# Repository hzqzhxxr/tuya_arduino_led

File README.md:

# tuya_arduino_led
This project is developed using Tuya SDK, which enables you to quickly develop branded apps connecting and controlling smart scenarios of many devices.

For more information, please check Tuya Developer Website.

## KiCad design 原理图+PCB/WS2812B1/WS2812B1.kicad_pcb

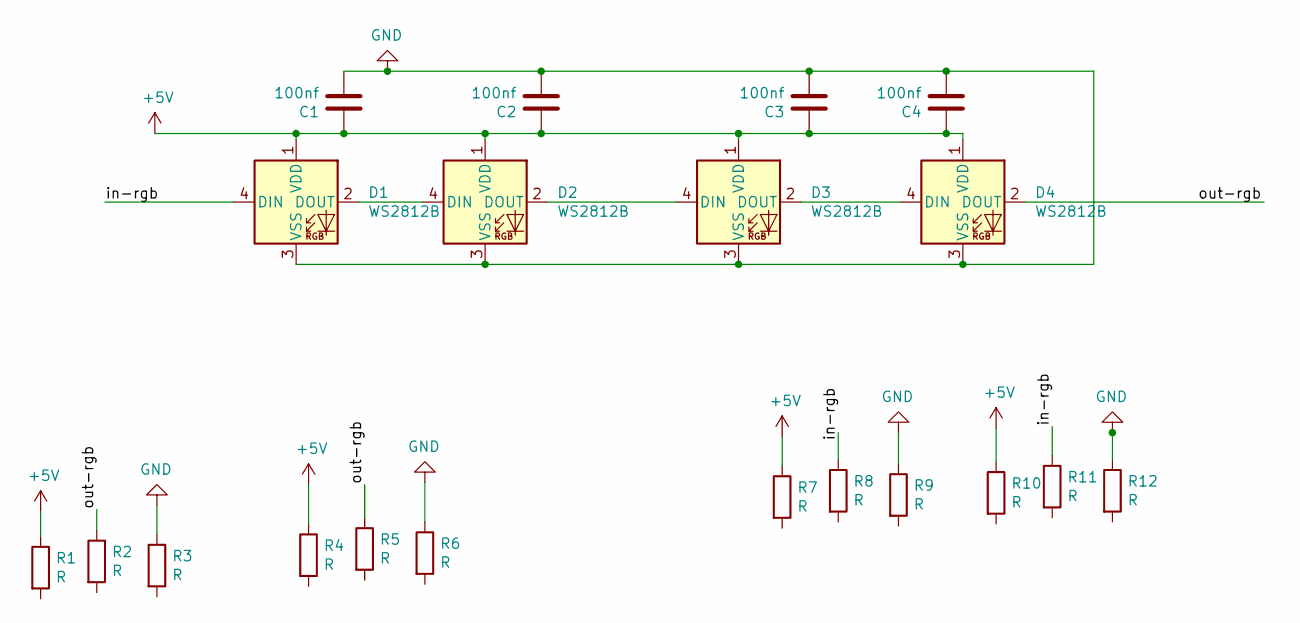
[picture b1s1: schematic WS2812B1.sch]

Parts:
C1, C2, C3, C4: 100nf; C_0603_1608Metric_Pad1.08x0.95mm_HandSolder
D1, D2, D3, D4: WS2812B; LED_WS2812B_PLCC4_5.0x5.0mm_P3.2mm
R1, R2, R3, R4, R5, R6, R7, R8, R9, R10, R11, R12: R; 焊接连接电阻

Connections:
+5V: C1.1, C2.1, C3.1, C4.1, D1.1 (VDD), D2.1 (VDD), D3.1 (VDD), D4.1 (VDD), R1.1, R4.1, R7.1, R10.1
/in-rgb: D1.4 (DIN), R8.1, R11.1
/out-rgb: D4.2 (DOUT), R2.1, R5.1
GND: C1.2, C2.2, C3.2, C4.2, D1.3 (VSS), D2.3 (VSS), D3.3 (VSS), D4.3 (VSS), R3.1, R6.1, R9.1, R12.1
unnamed: D1.2 (DOUT), D2.4 (DIN)
unnamed: D2.2 (DOUT), D3.4 (DIN)
unnamed: D3.2 (DOUT), D4.4 (DIN)

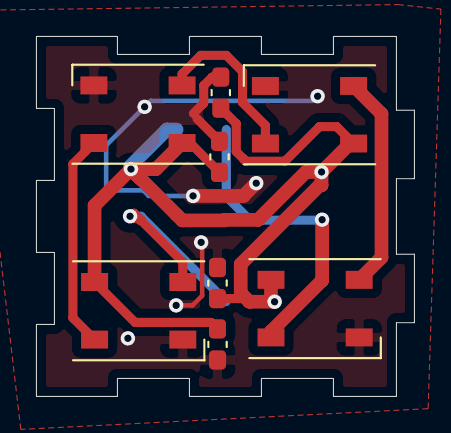
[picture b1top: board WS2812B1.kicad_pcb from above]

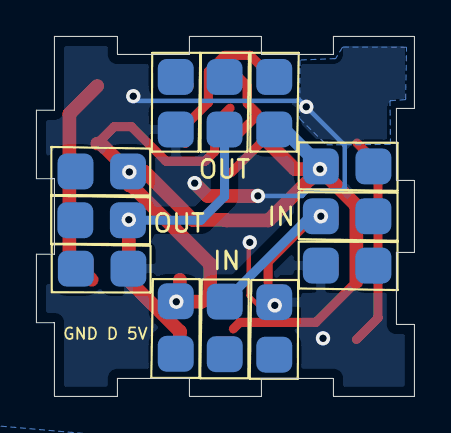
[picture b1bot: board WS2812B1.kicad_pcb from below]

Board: 2 copper layers, 21.0 x 20.0 mm, 20 parts (12 on the bottom side), 7 nets.

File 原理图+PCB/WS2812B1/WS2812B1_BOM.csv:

"Comment","Description","Designator","Footprint","LibRef","Pins","Quantity","PartNumber","url",
"100nf","desc","C1,C2,C3,C4,","C_0603_1608Metric_Pad1.08x0.95mm_HandSolder","libref","2","4","","",
"WS2812B","desc","D1,D2,D3,D4,","LED_WS2812B_PLCC4_5.0x5.0mm_P3.2mm","libref","4","4","","",
"Through Hole Items ",
"R","desc","R1,R2,R3,R4,R5,R6,R7,R8,R9,R10,R11,R12,","焊接连接电阻","libref","2","12","","",

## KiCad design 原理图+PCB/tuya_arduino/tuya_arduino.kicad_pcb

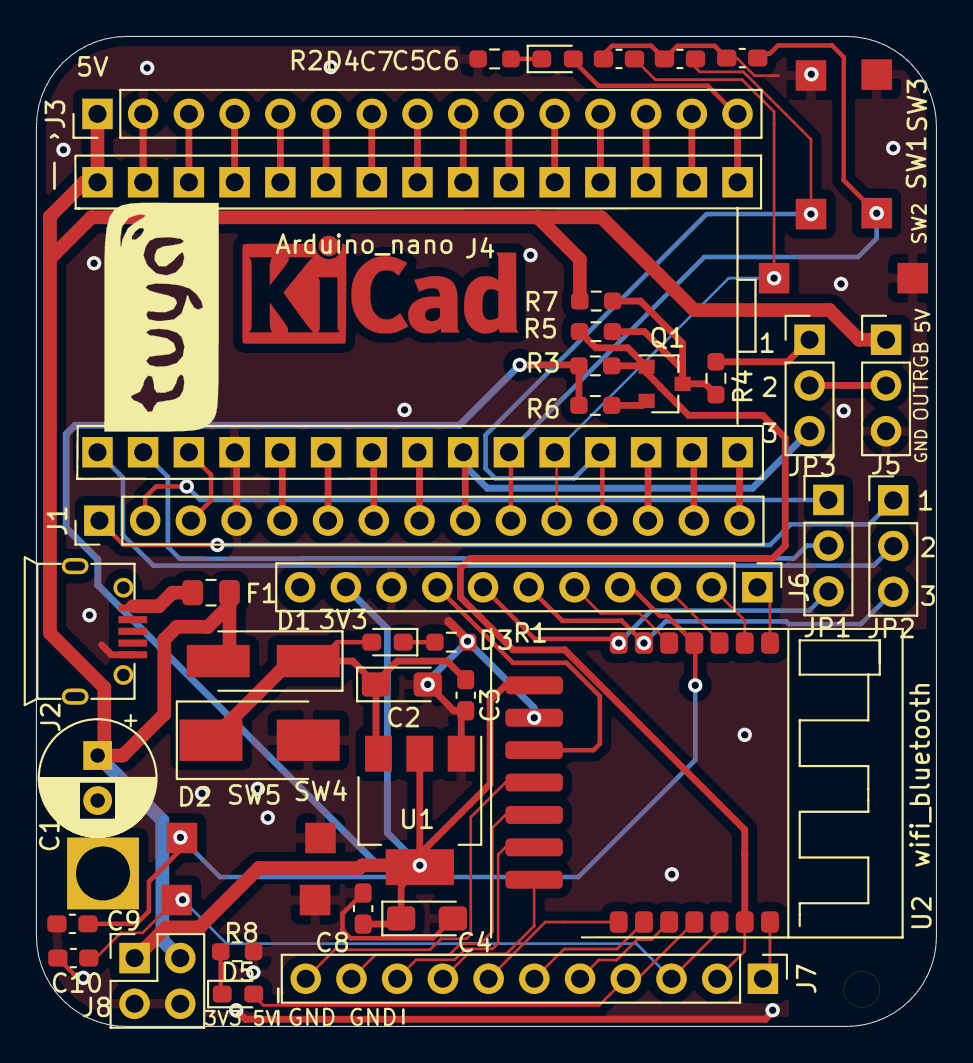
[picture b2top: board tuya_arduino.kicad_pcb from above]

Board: 2 copper layers, 50.0 x 55.0 mm, 43 parts (0 on the bottom side), 60 nets.

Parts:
C1: 220uf; CP_Radial_D6.3mm_P2.50mm
C2, C4: 22uf; CP_EIA-3216-18_Kemet-A_Pad1.58x1.35mm_HandSolder
C3, C5, C6, C7, C8, C9, C10: 0.1uf; C_0603_1608Metric_Pad1.08x0.95mm_HandSolder
D1: ss210; D_SMA_Handsoldering
D2: D_Zener; D_SMB_Handsoldering
D3, D4, D5: LED; LED_0603_1608Metric_Pad1.05x0.95mm_HandSolder
F1: Fuse; Fuse_0805_2012Metric_Pad1.15x1.40mm_HandSolder
J1, J3: Conn_01x15_Male; PinHeader_1x15_P2.54mm_Vertical
J2: USB_A; MicroUSB_5S_B_A01SB141B1-067
J4: arduino_nano_base; Arduino_nano_base
J5: Conn_01x03_Female; PinHeader_1x03_P2.54mm_Vertical
J6, J7: Conn_01x11_Male; PinHeader_1x11_P2.54mm_Vertical
J8: Conn_02x02_Top_Bottom_MountingPin; PinHeader_2x02_P2.54mm_Vertical
JP1, JP2, JP3: Jumper_NC_Dual; PinHeader_1x03_P2.54mm_Vertical
Q1: S8050; SOT-23
R1, R2: 330; R_0603_1608Metric_Pad0.98x0.95mm_HandSolder
R3, R6, R7: 2k; R_0603_1608Metric_Pad0.98x0.95mm_HandSolder
R4: 1R; R_0603_1608Metric_Pad0.98x0.95mm_HandSolder
R5: NC/0R; R_0603_1608Metric_Pad0.98x0.95mm_HandSolder
R8: 220; R_0603_1608Metric_Pad0.98x0.95mm_HandSolder
SW1, SW2, SW3, SW4, SW5: SW_Push; button_smd
U1: AMS1117-3.3; SOT-223-3_TabPin2
U2: mcu_tuya_cbu; tuya_cbu

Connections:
+3V3: C4.1, C8.1, J6.10, J8.1, R3.1, R6.1, U1.2, U2.14
+5V: C1.1, D1.2, F1.1, J3.1, J4.30, J5.1, J8.2, R7.1
/3V3: J3.14, J4.17
/5V: J3.4, J4.27
/A0: J3.12, J4.19
/A1: J3.11, J4.20
/A2: J3.10, J4.21
/A3: J3.9, J4.22
/A4: J3.8, J4.23
/A5: J3.7, J4.24
/A6: J3.6, J4.25
/A7: J3.5, J4.26
/ADC: J7.5, U2.5
/AREF: J3.13, J4.18
/D2: J1.5, J4.5
/D3: J1.6, J4.6
/D4: J1.7, J4.7
/D5: J1.8, J4.8
/D6: J1.9, J4.9, JP3.3
/D7: C6.1, J1.10, J4.10, SW3.1
/D8: C7.1, J1.11, J4.11, SW2.1
/D9: C5.1, J1.12, J4.12, SW1.1
/D10: J1.13, J4.13
/D11: J1.14, J4.14
/D12: J1.15, J4.15
/D13: D4.2, J3.15, J4.16
/KEY_TU: C10.1, J7.3, SW4.1, U2.3
/OUT_RGB: J5.2, JP3.2
/OUT_RGB_TU_3V3: J7.2, Q1.1, R3.2, R5.1, U2.2
/OUT_RGB_TU_5V: Q1.3, R4.1, R5.2, R7.2
/P6: J7.10, U2.10
/P7: J7.9, U2.9
/P8: J7.8, U2.8
/P9: J6.3, U2.19
/P14: J7.1, U2.1
/P15: J6.1, U2.21
/P17: J6.2, U2.20
/P22: D5.2, J7.4, U2.4
/P24: J6.8, U2.12
/P26: J7.11, U2.11
/P28: J6.5, U2.17
/RESET: J3.3, J4.28
/RST: J1.3, J4.3
/RST_TU,CEN: C9.1, J6.4, SW5.1, U2.18
/RX: J4.2, JP1.2
/RX2: J7.6, U2.6
/RX_C: J6.6, JP2.3, U2.16
/RX_D: J1.2, JP1.1
/TX: J4.1, JP2.2
/TX2: J7.7, U2.7
/TX_C: J6.7, JP1.3, U2.15
/TX_D: J1.1, JP2.1
GND: C2.2, C3.2, C4.2, C5.2, C6.2, C7.2, C8.2, C9.2, C10.2, D2.2, J1.4, J2.5, J3.2, J4.4, J4.29, J5.3, J6.9, J8.3, J8.4, R1.2, R2.2, R8.2, SW1.2, SW2.2, SW3.2, SW4.2, SW5.2, U1.1, U2.13
unnamed: C2.1, C3.1, D1.1, D2.1, D3.2, U1.3
unnamed: D3.1, R1.1
unnamed: D4.1, R2.1
unnamed: D5.1, R8.1
unnamed: F1.2, J2.1
unnamed: JP3.1, R4.2
unnamed: Q1.2, R6.2

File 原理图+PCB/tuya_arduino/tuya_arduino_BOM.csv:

"Comment","Description","Designator","Footprint","LibRef","Pins","Quantity","PartNumber","url",
"22uf","desc","C2,C4,","CP_EIA-3216-18_Kemet-A_Pad1.58x1.35mm_HandSolder","libref","2","2","","",
"0.1uf","desc","C3,C5,C6,C7,C8,C9,C10,","C_0603_1608Metric_Pad1.08x0.95mm_HandSolder","libref","2","7","","",
"ss210","desc","D1,","D_SMA_Handsoldering","libref","2","1","","",
"D_Zener","desc","D2,","D_SMB_Handsoldering","libref","2","1","","",
"LED","desc","D3,D4,D5,","LED_0603_1608Metric_Pad1.05x0.95mm_HandSolder","libref","2","3","","",
"Fuse","desc","F1,","Fuse_0805_2012Metric_Pad1.15x1.40mm_HandSolder","libref","2","1","","",
"S8050","desc","Q1,","SOT-23","libref","3","1","","",
"330","desc","R1,R2,","R_0603_1608Metric_Pad0.98x0.95mm_HandSolder","libref","2","2","","",
"2k","desc","R3,R6,R7,","R_0603_1608Metric_Pad0.98x0.95mm_HandSolder","libref","2","3","","",
"1R","desc","R4,","R_0603_1608Metric_Pad0.98x0.95mm_HandSolder","libref","2","1","","",
"NC/0R","desc","R5,","R_0603_1608Metric_Pad0.98x0.95mm_HandSolder","libref","2","1","","",
"220","desc","R8,","R_0603_1608Metric_Pad0.98x0.95mm_HandSolder","libref","2","1","","",
"AMS1117-3.3","desc","U1,","SOT-223-3_TabPin2","libref","4","1","","",
"mcu_tuya_cbu","desc","U2,","tuya_cbu","libref","21","1","","",
"SW_Push","desc","SW1,SW2,SW3,SW4,SW5,","button_smd","libref","2","5","","",
"LOGO","desc","G***,","tuya-logo","libref","0","1","","",
"KiCad-Logo_6mm_Copper","desc","REF**,","KiCad-Logo_6mm_Copper","libref","0","1","","",
"Through Hole Items ",
"220uf","desc","C1,","CP_Radial_D6.3mm_P2.50mm","libref","2","1","","",
"Conn_01x15_Male","desc","J1,J3,","PinHeader_1x15_P2.54mm_Vertical","libref","15","2","","",
"USB_A","desc","J2,","MicroUSB_5S_B_A01SB141B1-067","libref","9","1","","",
"arduino_nano_base","desc","J4,","Arduino_nano_base","libref","30","1","","",
"Conn_01x03_Female","desc","J5,","PinHeader_1x03_P2.54mm_Vertical","libref","3","1","","",
"Conn_01x11_Male","desc","J6,J7,","PinHeader_1x11_P2.54mm_Vertical","libref","11","2","","",
"Conn_02x02_Top_Bottom_MountingPin","desc","J8,","PinHeader_2x02_P2.54mm_Vertical","libref","4","1","","",
"Jumper_NC_Dual","desc","JP1,JP2,JP3,","PinHeader_1x03_P2.54mm_Vertical","libref","3","3","","",
"HOLE_2MM","desc","REF**,","HOLE_2MM","libref","1","1","","",
"MP_HOLE_L4_M3","desc","REF**,","MP_HOLE_L4_M3","libref","1","1","","",
